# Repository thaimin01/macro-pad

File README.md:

DEMO VIDEO HERE: https://www.youtube.com/watch?v=82zxsW1auBI

Custom RP2040 Macro Pad
An open-source, portable macro pad designed to increases and decreases volume in a convenient way and comes with custom key mapping.

Features
 -Xiao seeed rp2040
 
 -9 switches
 
 -1 OLED 0.91'' 128x32 SSD1306

 -1 Rotary encoder

Many keys to play around with

You can custom the key mapping, uses of each keys and utilize it

Quick, convenient, volume control rotary encoder
Volume controls designed to change system volume quickly and accurately.

A customizable screen
An OLED 0.91 inch screen that you can cutomize on your own ! e.g Animations, Drawings, etc.

USB-C Connectivity
Uses a modern USB-C interface for HID communication with your computer

Firmware

Runs on C++, with built in Adafruit_TinyUSB.h, It works by taking instruction from the buttons and translate it in to HID signal for the computer

Schematic

Case

Never ever ask an engineer to disign a case

This is a simple case but its done

Bill Of Materials

| Reference | Qty | Value | DNP | Exclude fr... | Exclude fr... | Footprint | Datasheet |
| :--- | :--- | :--- | :--- | :--- | :--- | :--- | :--- |
| D1, D2, D5, D6 | 4 | SK6812MINI-E | | | | LED_SMD:SK6812MINI-E | [Link](https://www.lcsc.com/datasheet/C5149201.pdf) |
| D7, D8, D9, D10, D11, D12, D13, D14, D15 | 9 | 1N4148 | | | | Diode_THT:D_DO-35_SOD27_P7.62mm_Horizontal | [Link](https://assets.nexperia.com/documents/data-sheet/1N4148_1N4448.pdf) |
| J1 | 1 | Conn_01x04_Pin | | | | oled:SSD1306-0.91-OLED-4pin-128x32 | |
| MX1 | 1 | 0,0 | | | | marbastlib-xp-mx:SW_MX_Reversible_1u | |
| MX2 | 1 | 0,1 | | | | marbastlib-xp-mx:SW_MX_Reversible_1u | |
| MX3 | 1 | 0,2 | | | | marbastlib-xp-mx:SW_MX_Reversible_1u | |
| MX4 | 1 | 1,0 | | | | marbastlib-xp-mx:SW_MX_Reversible_1u | |
| MX5 | 1 | 1,1 | | | | marbastlib-xp-mx:SW_MX_Reversible_1u | |
| MX6 | 1 | 1,2 | | | | marbastlib-xp-mx:SW_MX_Reversible_1u | |
| MX7 | 1 | 2,0 | | | | marbastlib-xp-mx:SW_MX_Reversible_1u | |
| MX8 | 1 | 2,1 | | | | marbastlib-xp-mx:SW_MX_Reversible_1u | |
| MX9 | 1 | 2,2 | | | | marbastlib-xp-mx:SW_MX_Reversible_1u | |
| SW1 | 1 | RotaryEncoder_Switch_MP | | | | Rotary_Encoder:RotaryEncoder_Alps_EC11E-Switch_Vertical_H20mm_CircularMountingHoles | |
| U1 | 1 | XIAO-RP2040-SMD | | | | Seeed_Studio_XIAO_Series:XIAO-RP2040-SMD | |

Coding interface

Code by a Human, on Arduino IDE, And C++ !!!

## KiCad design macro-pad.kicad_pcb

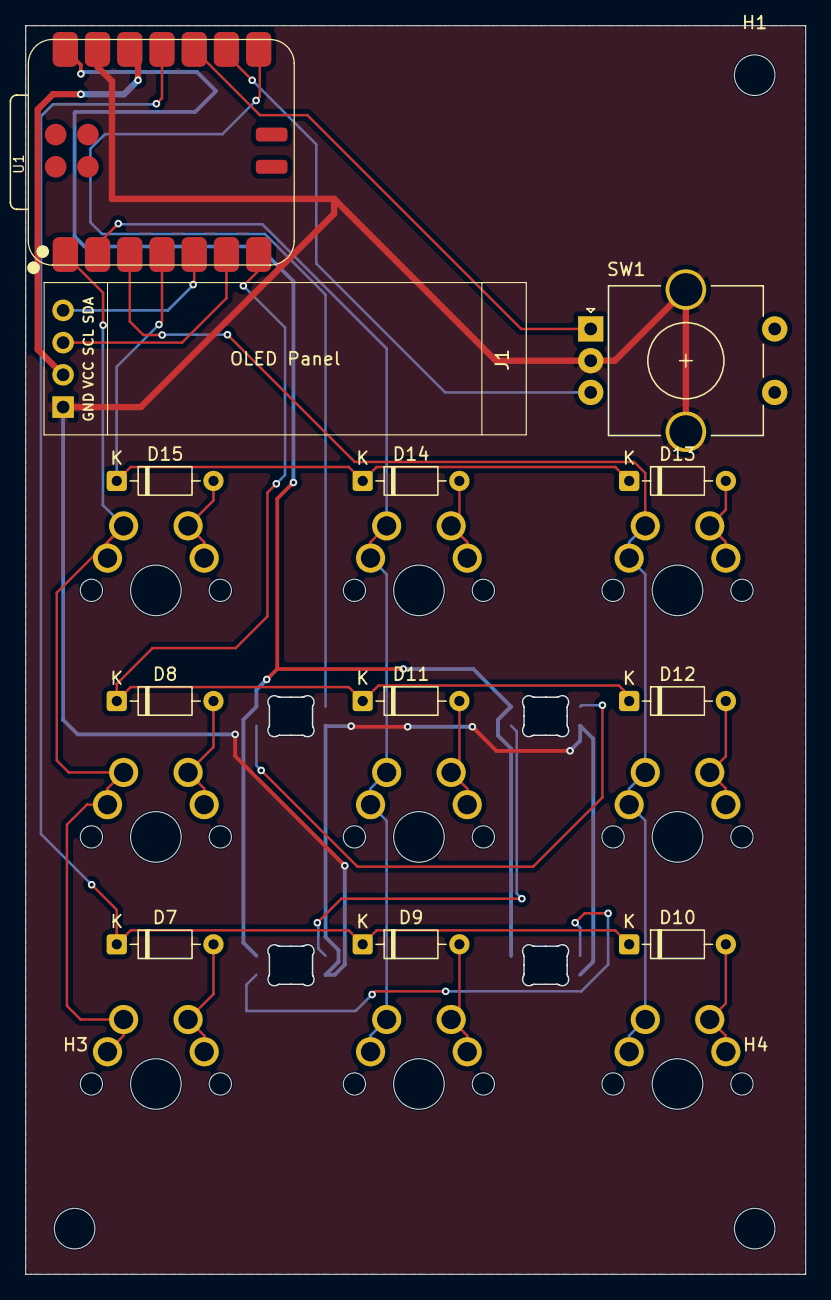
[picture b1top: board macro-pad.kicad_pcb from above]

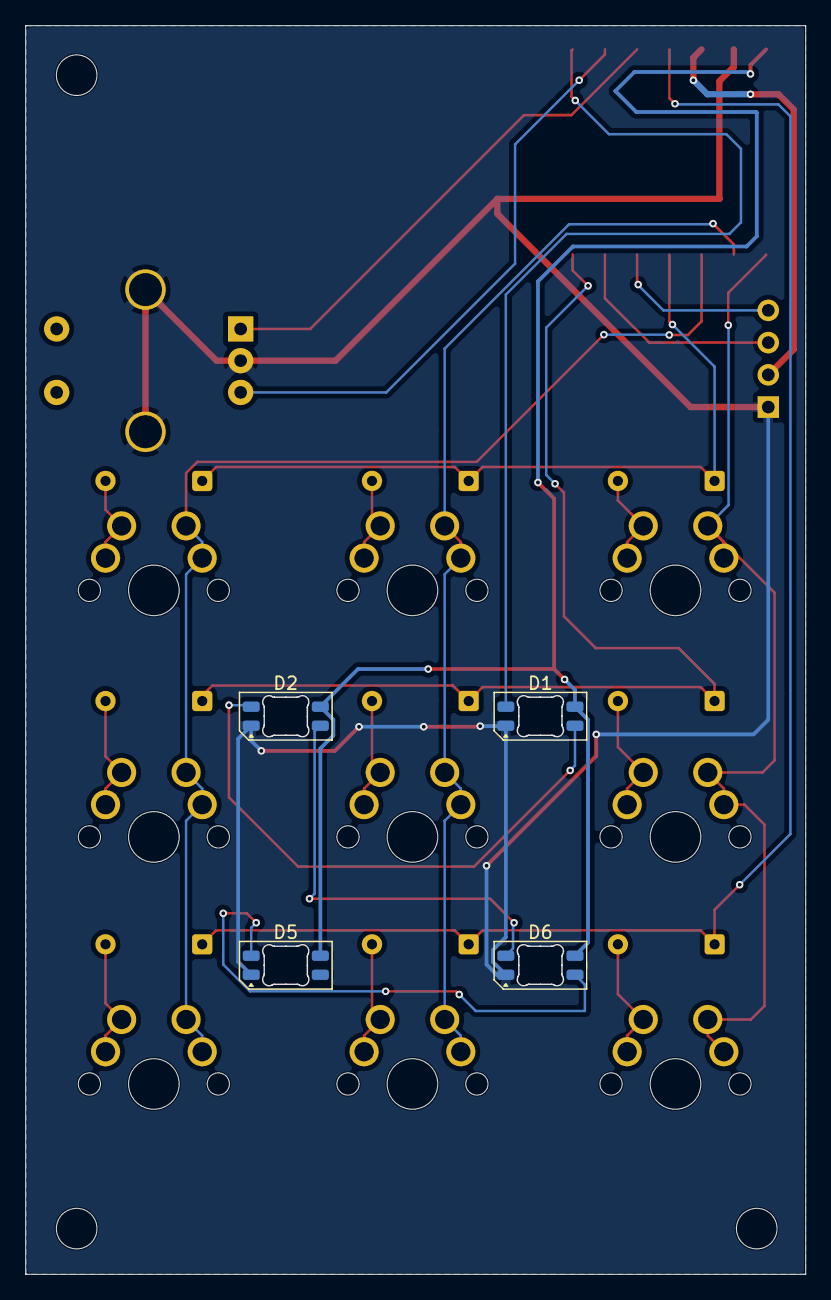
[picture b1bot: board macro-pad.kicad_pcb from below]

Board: 2 copper layers, 61.5 x 98.4 mm, 28 parts (4 on the bottom side), 26 nets.

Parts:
D1, D2, D5, D6: SK6812MINI-E; LED_SK6812MINI-E_3.2x2.8mm_P1.5mm_ReverseMount
D7, D8, D9, D10, D11, D12, D13, D14, D15: 1N4148; D_DO-35_SOD27_P7.62mm_Horizontal
H1, H3, H4: MountingHole; MountingHole_3.2mm_M3
J1: Conn_01x04_Pin; SSD1306-0.91-OLED-4pin-128x32
MX1: 0,0; SW_MX_Reversible_1u
MX2: 0,1; SW_MX_Reversible_1u
MX3: 0,2; SW_MX_Reversible_1u
MX4: 1,0; SW_MX_Reversible_1u
MX5: 1,1; SW_MX_Reversible_1u
MX6: 1,2; SW_MX_Reversible_1u
MX7: 2,0; SW_MX_Reversible_1u
MX8: 2,1; SW_MX_Reversible_1u
MX9: 2,2; SW_MX_Reversible_1u
SW1: RotaryEncoder_Switch_MP; RotaryEncoder_Alps_EC11E-Switch_Vertical_H20mm_CircularMoun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
U1: XIAO-RP2040-SMD

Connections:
3V3: J1.2, U1.12 (3V3_OUT)
5V: D1.3 (VDD), D2.3 (VDD), D5.3 (VDD), D6.3 (VDD), U1.14 (VBUS)
Column 0: MX1.1, MX2.1, MX3.1, U1.1 (D0)
Column 1: MX4.1, MX5.1, MX6.1, U1.2 (D1)
Column 2: MX7.1, MX8.1, MX9.1, U1.3 (D2)
GND: D1.1 (VSS), D2.1 (VSS), D5.1 (VSS), D6.1 (VSS), J1.1, SW1.C, SW1.MP, U1.13 (GND)
LED INPUT: D1.2 (DIN), U1.8 (D7)
unnamed: D1.4 (DOUT), D2.2 (DIN)
unnamed: D2.4 (DOUT), D6.2 (DIN)
unnamed: D5.2 (DIN), D6.4 (DOUT)
unnamed: D7.2 (A), MX3.2
unnamed: D8.2 (A), MX2.2
unnamed: D9.2 (A), MX6.2
unnamed: D10.2 (A), MX9.2
unnamed: D11.2 (A), MX5.2
unnamed: D12.2 (A), MX8.2
unnamed: D13.2 (A), MX7.2
unnamed: D14.2 (A), MX4.2
unnamed: D15.2 (A), MX1.2
Row 0: D13.1 (K), D14.1 (K), D15.1 (K), U1.4 (D3)
Row 1: D8.1 (K), D11.1 (K), D12.1 (K), U1.7 (D6)
Row 2: D7.1 (K), D9.1 (K), D10.1 (K), U1.11 (D10)
SCL: J1.3, U1.6 (D5)
SDA: J1.4, U1.5 (D4)
Signal 1: SW1.A, U1.10 (D9)
Signal 2: SW1.B, U1.9 (D8)

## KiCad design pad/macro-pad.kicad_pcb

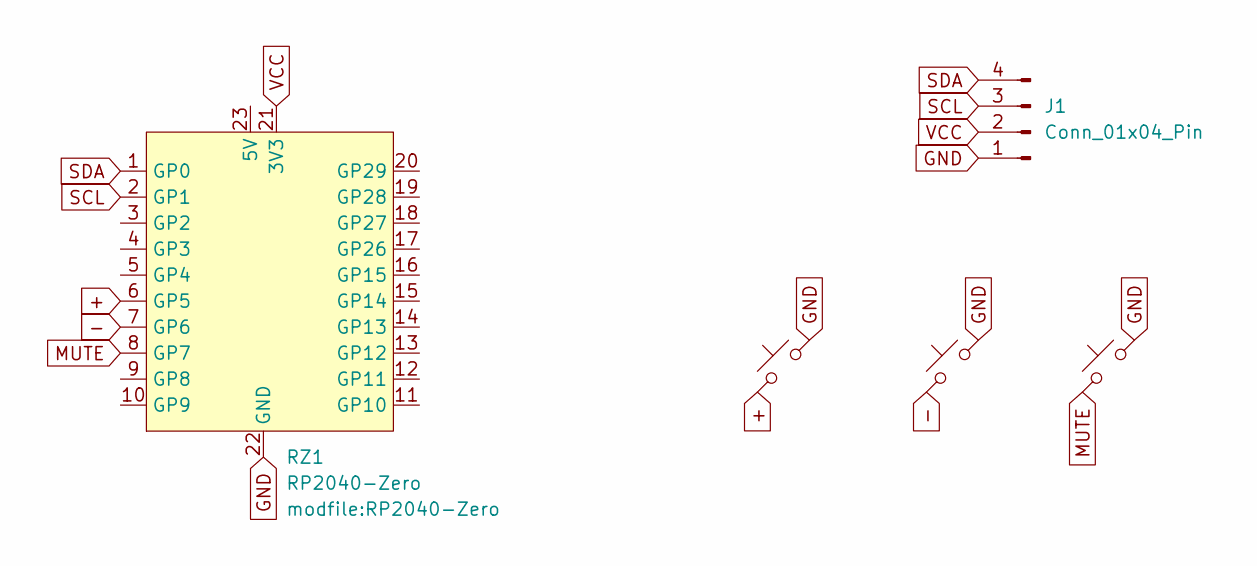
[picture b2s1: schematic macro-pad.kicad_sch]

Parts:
J1: Conn_01x04_Pin; SSD1306-0.91-OLED-4pin-128x32
MX1, MX2, MX3: MX_SW_HS; SW_MX_HS_CPG151101S11_1u
RZ1: RP2040-Zero

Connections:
+: MX1.1, RZ1.6 (GP5)
-: MX3.1, RZ1.7 (GP6)
GND: J1.1, MX1.2, MX2.2, MX3.2, RZ1.22 (GND)
MUTE: MX2.1, RZ1.8 (GP7)
SCL: J1.3, RZ1.2 (GP1)
SDA: J1.4, RZ1.1 (GP0)
VCC: J1.2, RZ1.21 (3V3)

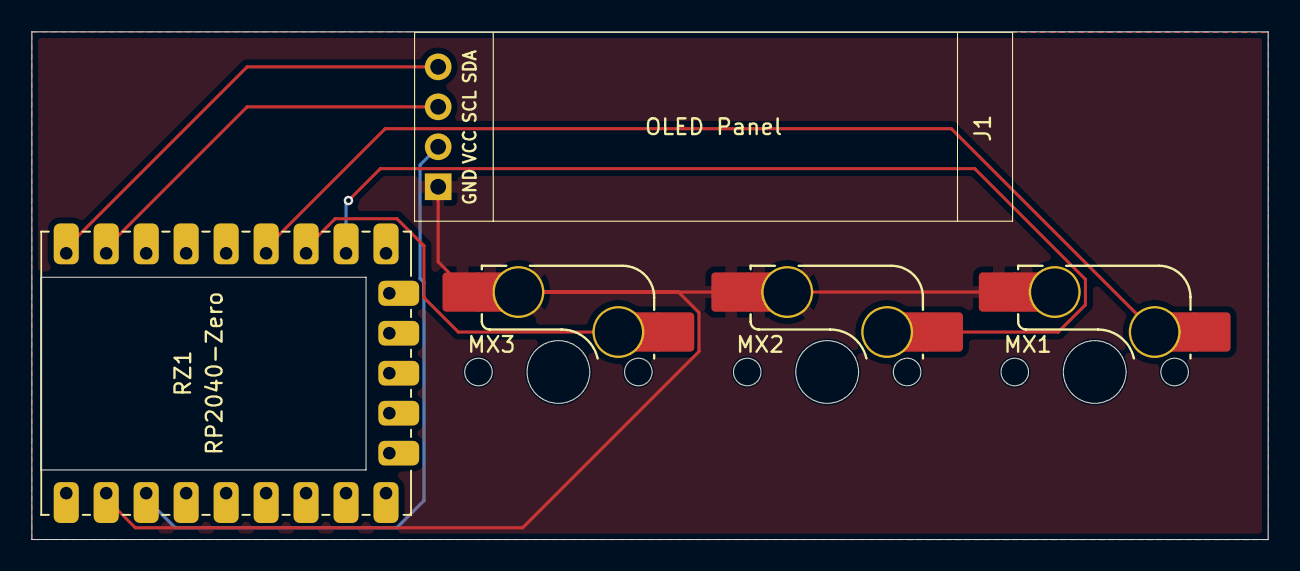
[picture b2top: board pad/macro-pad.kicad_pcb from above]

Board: 2 copper layers, 78.6 x 32.3 mm, 5 parts (0 on the bottom side), 7 nets.

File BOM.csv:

"Reference","Qty","Value","DNP","Exclude from BOM","Exclude from Board","Footprint","Datasheet"
"J1","1","Conn_01x04_Pin","","","","oled:SSD1306-0.91-OLED-4pin-128x32",""
"MX1,MX2,MX3","3","MX_SW_HS","","","","marbastlib-mx:SW_MX_HS_CPG151101S11_1u",""
"RZ1","1","RP2040-Zero","","","","modfile:RP2040-Zero",""
